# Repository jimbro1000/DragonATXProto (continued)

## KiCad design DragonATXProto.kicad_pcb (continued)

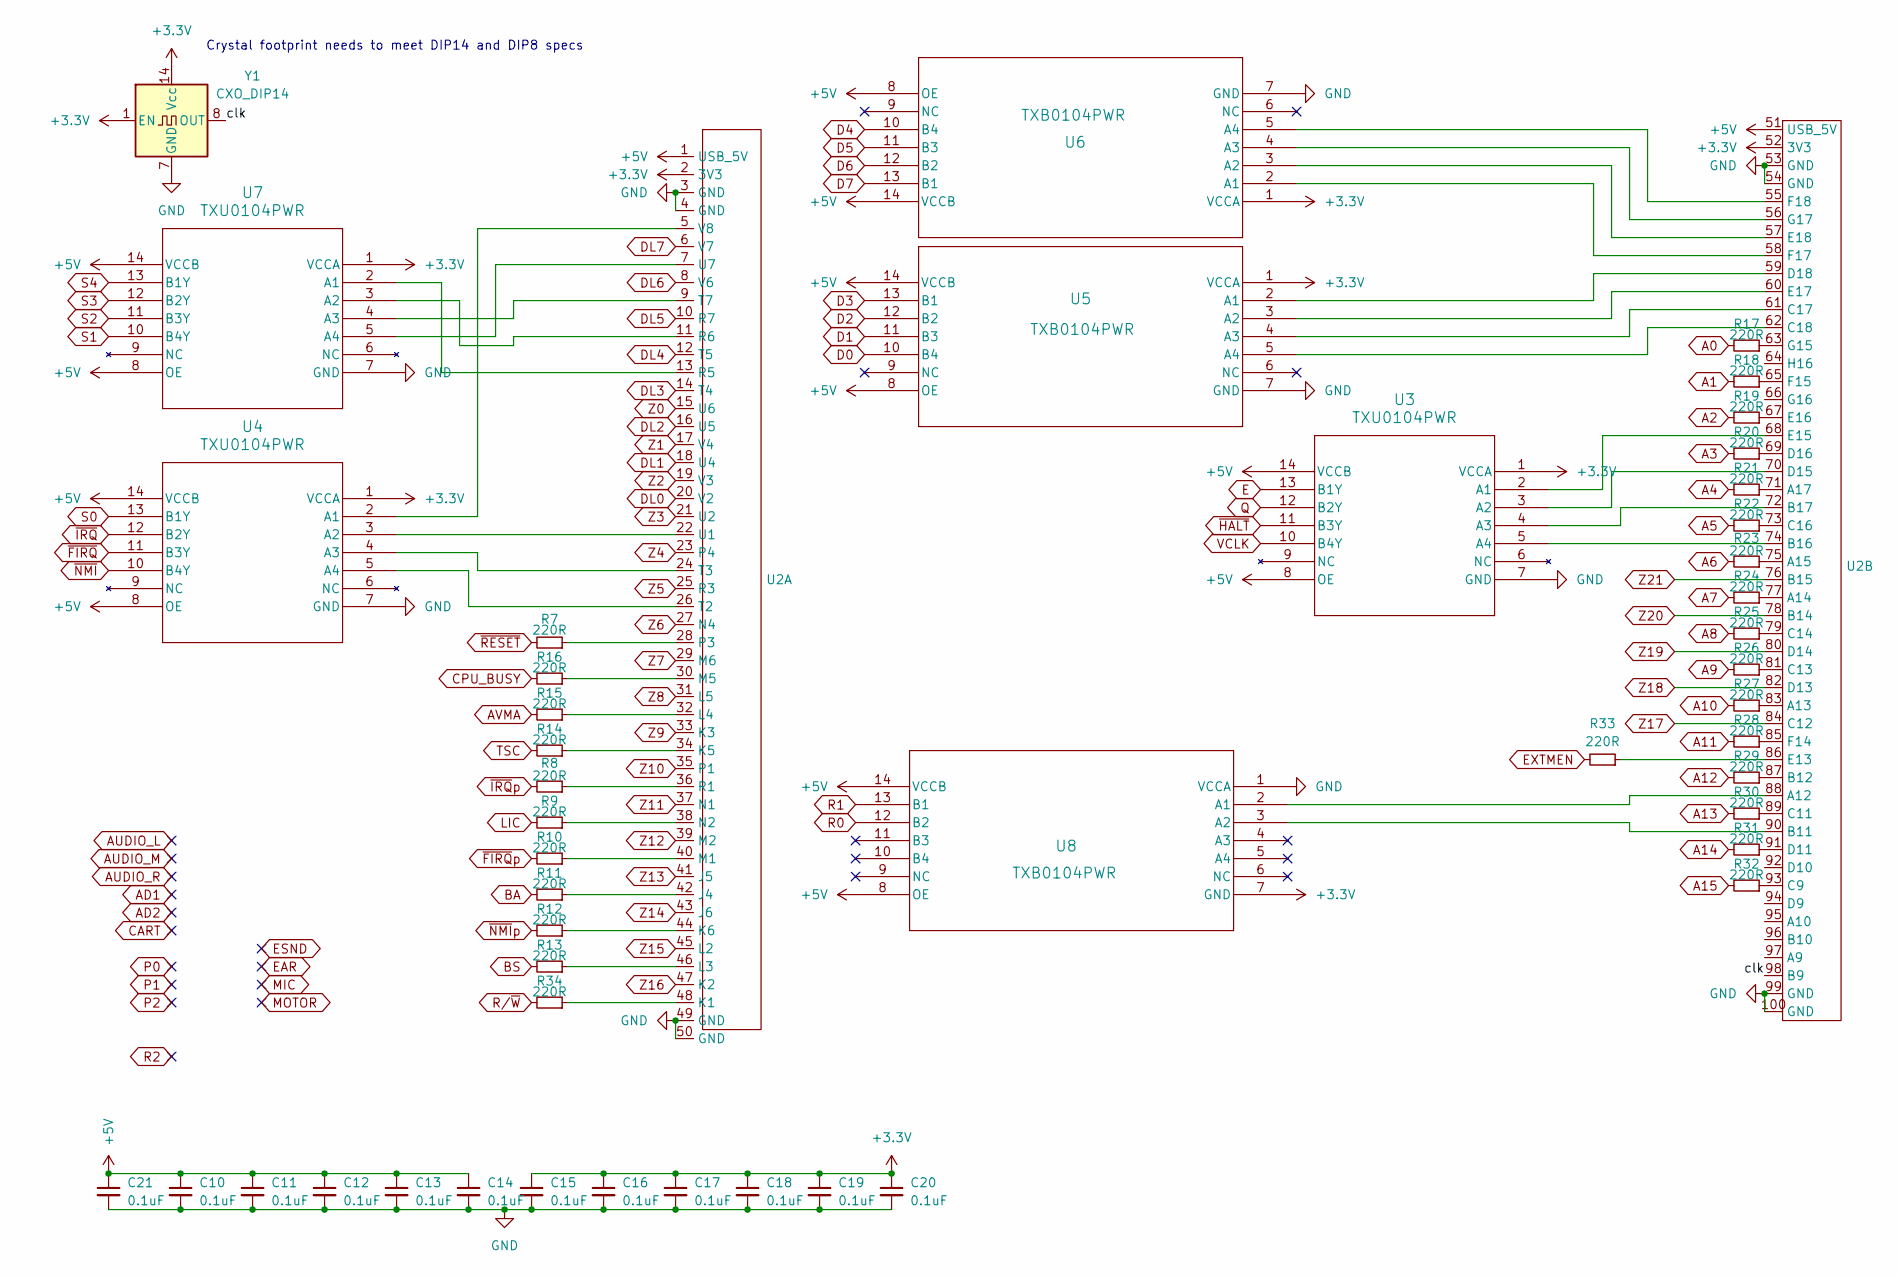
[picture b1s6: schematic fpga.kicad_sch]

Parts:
C10, C11, C12, C13, C14, C15, C16, C17, C18, C19, C20, C21: 0.1uF; C_0603_1608Metric
R7, R8, R9, R10, R11, R12, R13, R14, R15, R16, R17, R18, R19, R20, R21, R22, R23, R24, R25, R26, R27, R28, R29, R30, R31, R32, R33, R34: 220R; R_0603_1608Metric
U2: QMTECH_XC7A15T
U3, U4, U7: TXU0104PWR; TSSOP_0104PWR
U5, U6, U8: TXB0104PWR; TSSOP_0104PWR
Y1: CXO_DIP14; Oscillator_DIP-14

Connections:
+3.3V: C15.1, C16.1, C17.1, C18.1, C19.1, C20.1, U2.2 (3V3), U2.52 (3V3), U3.1 (VCCA), U4.1 (VCCA), U5.1 (VCCA), U6.1 (VCCA), U7.1 (VCCA), U8.7 (GND), Y1.1 (EN), Y1.14 (Vcc); also elsewhere on the board
+5V: C10.1, C11.1, C12.1, C13.1, C14.1, C21.1, U2.1 (USB_5V), U2.51 (USB_5V), U3.8 (OE), U3.14 (VCCB), U4.8 (OE), U4.14 (VCCB), U5.8 (OE), U5.14 (VCCB), U6.8 (OE), U6.14 (VCCB), U7.8 (OE), U7.14 (VCCB), U8.8 (OE), U8.14 (VCCB); also elsewhere on the board
/fpga/clk: U2.98 (B9), Y1.8 (OUT)
A0: R17.2; also elsewhere on the board
A1: R18.2; also elsewhere on the board
A2: R19.2; also elsewhere on the board
A3: R20.2; also elsewhere on the board
A4: R21.2; also elsewhere on the board
A5: R22.2; also elsewhere on the board
A6: R23.2; also elsewhere on the board
A7: R24.2; also elsewhere on the board
A8: R25.2; also elsewhere on the board
A9: R26.2; also elsewhere on the board
A10: R27.2; also elsewhere on the board
A11: R28.2; also elsewhere on the board
A12: R29.2; also elsewhere on the board
A13: R30.2; also elsewhere on the board
A14: R31.2; also elsewhere on the board
A15: R32.2; also elsewhere on the board
AVMA: R15.2; also elsewhere on the board
BA: R11.2; also elsewhere on the board
BS: R13.2; also elsewhere on the board
CPU_BUSY: R16.2; also elsewhere on the board
D0: U5.10 (B4); also elsewhere on the board
D1: U5.11 (B3); also elsewhere on the board
D2: U5.12 (B2); also elsewhere on the board
D3: U5.13 (B1); also elsewhere on the board
D4: U6.10 (B4); also elsewhere on the board
D5: U6.11 (B3); also elsewhere on the board
D6: U6.12 (B2); also elsewhere on the board
D7: U6.13 (B1); also elsewhere on the board
DL0: U2.20 (V2); also elsewhere on the board
DL1: U2.18 (U4); also elsewhere on the board
DL2: U2.16 (U5); also elsewhere on the board
DL3: U2.14 (T4); also elsewhere on the board
DL4: U2.12 (T5); also elsewhere on the board
DL5: U2.10 (R7); also elsewhere on the board
DL6: U2.8 (V6); also elsewhere on the board
DL7: U2.6 (V7); also elsewhere on the board
E: U3.13 (B1Y); also elsewhere on the board
EXTMEN: R33.2; also elsewhere on the board
GND: C10.2, C11.2, C12.2, C13.2, C14.2, C15.2, C16.2, C17.2, C18.2, C19.2, C20.2, C21.2, U2.3 (GND), U2.4 (GND), U2.49 (GND), U2.50 (GND), U2.53 (GND), U2.54 (GND), U2.99 (GND), U2.100 (GND), U3.7 (GND), U4.7 (GND), U5.7 (GND), U6.7 (GND), U7.7 (GND), U8.1 (VCCA), Y1.7 (GND); also elsewhere on the board
LIC: R9.2; also elsewhere on the board
unnamed: R11.1, U2.42 (J4)
unnamed: R34.1, U2.48 (K1)
unnamed: R14.1, U2.34 (K5)
unnamed: R12.1, U2.44 (K6)
unnamed: R13.1, U2.46 (L3)
unnamed: R15.1, U2.32 (L4)
unnamed: R10.1, U2.40 (M1)
unnamed: R16.1, U2.30 (M5)
unnamed: R9.1, U2.38 (N2)
unnamed: R7.1, U2.28 (P3)
unnamed: R8.1, U2.36 (R1)
unnamed: U2.13 (R5), U7.2 (A1)
unnamed: U2.11 (R6), U7.3 (A2)
unnamed: U2.26 (T2), U4.5 (A4)
unnamed: U2.24 (T3), U4.4 (A3)
unnamed: U2.9 (T7), U7.4 (A3)
unnamed: U2.22 (U1), U4.3 (A2)
unnamed: U2.7 (U7), U7.5 (A4)
unnamed: U2.5 (V8), U4.2 (A1)
unnamed: U2.88 (A12), U8.2 (A1)
unnamed: R27.1, U2.83 (A13)
unnamed: R24.1, U2.77 (A14)
unnamed: R23.1, U2.75 (A15)
unnamed: R21.1, U2.71 (A17)
unnamed: U2.90 (B11), U8.3 (A2)
unnamed: R29.1, U2.87 (B12)
unnamed: U2.74 (B16), U3.5 (A4)
unnamed: U2.72 (B17), U3.4 (A3)
unnamed: R32.1, U2.93 (C9)
unnamed: R30.1, U2.89 (C11)
unnamed: R26.1, U2.81 (C13)
unnamed: R25.1, U2.79 (C14)
unnamed: R22.1, U2.73 (C16)
unnamed: U2.61 (C17), U5.4 (A3)
unnamed: U2.62 (C18), U5.5 (A4)
unnamed: R31.1, U2.91 (D11)
unnamed: U2.70 (D15), U3.3 (A2)
unnamed: R20.1, U2.69 (D16)
unnamed: U2.59 (D18), U5.2 (A1)
unnamed: R33.1, U2.86 (E13)
unnamed: U2.68 (E15), U3.2 (A1)
unnamed: R19.1, U2.67 (E16)
unnamed: U2.60 (E17), U5.3 (A2)
unnamed: U2.57 (E18), U6.3 (A2)
unnamed: R28.1, U2.85 (F14)
unnamed: R18.1, U2.65 (F15)
unnamed: U2.58 (F17), U6.2 (A1)
unnamed: U2.55 (F18), U6.5 (A4)
unnamed: R17.1, U2.63 (G15)
unnamed: U2.56 (G17), U6.4 (A3)
Q: U3.12 (B2Y); also elsewhere on the board
R0: U8.12 (B2); also elsewhere on the board
R1: U8.13 (B1); also elsewhere on the board
R/~W: R34.2; also elsewhere on the board
S0: U4.13 (B1Y); also elsewhere on the board
S1: U7.10 (B4Y); also elsewhere on the board
S2: U7.11 (B3Y); also elsewhere on the board
S3: U7.12 (B2Y); also elsewhere on the board
S4: U7.13 (B1Y); also elsewhere on the board
TSC: R14.2; also elsewhere on the board
VCLK: U3.10 (B4Y); also elsewhere on the board
Z0: U2.15 (U6); also elsewhere on the board
Z1: U2.17 (V4); also elsewhere on the board
Z2: U2.19 (V3); also elsewhere on the board
Z3: U2.21 (U2); also elsewhere on the board
Z4: U2.23 (P4); also elsewhere on the board
Z5: U2.25 (R3); also elsewhere on the board
Z6: U2.27 (N4); also elsewhere on the board
Z7: U2.29 (M6); also elsewhere on the board
Z8: U2.31 (L5); also elsewhere on the board
Z9: U2.33 (K3); also elsewhere on the board
Z10: U2.35 (P1); also elsewhere on the board
Z11: U2.37 (N1); also elsewhere on the board
Z12: U2.39 (M2); also elsewhere on the board
Z13: U2.41 (J5); also elsewhere on the board
Z14: U2.43 (J6); also elsewhere on the board
Z15: U2.45 (L2); also elsewhere on the board
Z16: U2.47 (K2); also elsewhere on the board
Z17: U2.84 (C12); also elsewhere on the board
Z18: U2.82 (D13); also elsewhere on the board
Z19: U2.80 (D14); also elsewhere on the board
Z20: U2.78 (B14); also elsewhere on the board
Z21: U2.76 (B15); also elsewhere on the board
~FIRQ: U4.11 (B3Y); also elsewhere on the board
~FIRQp: R10.2; also elsewhere on the board
~HALT: U3.11 (B3Y); also elsewhere on the board
~IRQ: U4.12 (B2Y); also elsewhere on the board
~IRQp: R8.2; also elsewhere on the board
~NMI: U4.10 (B4Y); also elsewhere on the board
~NMIp: R12.2; also elsewhere on the board
~RESET: R7.2; also elsewhere on the board

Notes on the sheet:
Crystal footprint needs to meet DIP14 and DIP8 specs

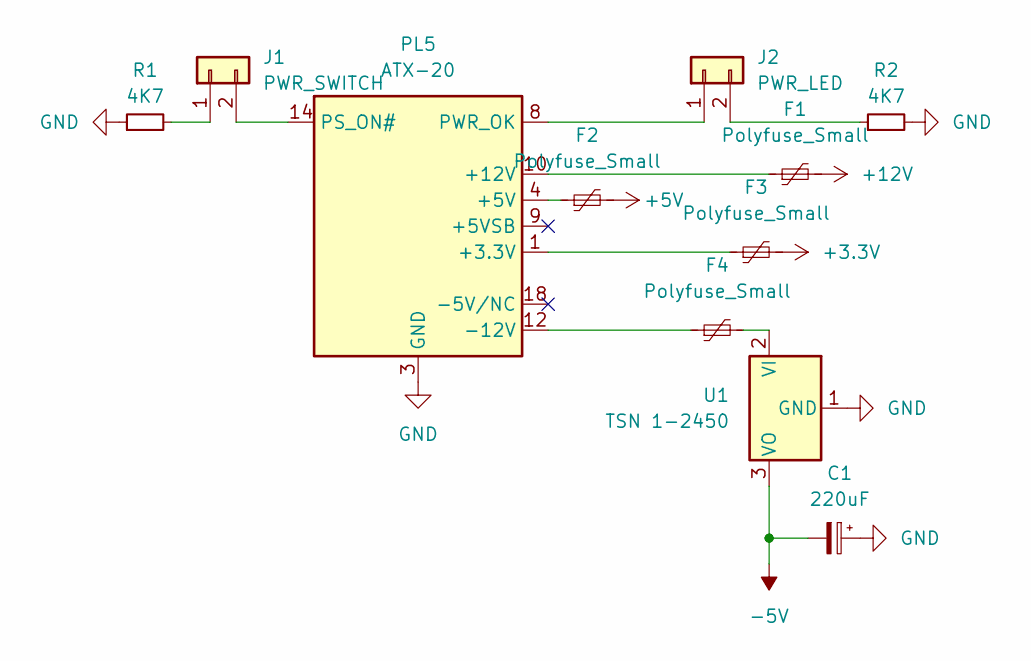
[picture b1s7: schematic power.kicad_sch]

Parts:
C1: 220uF; CP_Radial_D8.0mm_P5.00mm; DigiKey 732-875575345004CT-ND
F1, F2, F3, F4: Polyfuse_Small; Fuse_Bourns_MF-RHT400
J1: PWR_SWITCH; PinHeader_1x02_P2.54mm_Vertical
J2: PWR_LED; PinHeader_1x02_P2.54mm_Vertical
PL5: ATX-20; Molex_Mini-Fit_Jr_5566-20A_2x10_P4.20mm_Vertical
R1, R2: 4K7; R_Axial_DIN0204_L3.6mm_D1.6mm_P2.54mm_Vertical; DigiKey 541-4131-1-ND
U1: TSN 1-2450; TO-220-3_Horizontal_TabDown; DigiKey TSN1-2450-ND

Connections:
+3.3V: F3.2; also elsewhere on the board
+5V: F2.2; also elsewhere on the board
+12V: F1.2; also elsewhere on the board
-5V: C1.2, U1.3 (VO); also elsewhere on the board
GND: C1.1, PL5.3 (GND), PL5.5 (GND), PL5.7 (GND), PL5.13 (GND), PL5.15 (GND), PL5.16 (GND), PL5.17 (GND), R1.1, R2.2, U1.1 (GND); also elsewhere on the board
unnamed: F2.1, PL5.4 (+5V), PL5.6 (+5V), PL5.19 (+5V), PL5.20 (+5V)
unnamed: F3.1, PL5.1 (+3.3V), PL5.2 (+3.3V), PL5.11 (+3.3V)
unnamed: J1.1, R1.2
unnamed: J1.2, PL5.14 (PS_ON#)
unnamed: J2.1, PL5.8 (PWR_OK)
unnamed: J2.2, R2.1
unnamed: F1.1, PL5.10 (+12V)
unnamed: F4.1, PL5.12 (-12V)
unnamed: F4.2, U1.2 (VI)

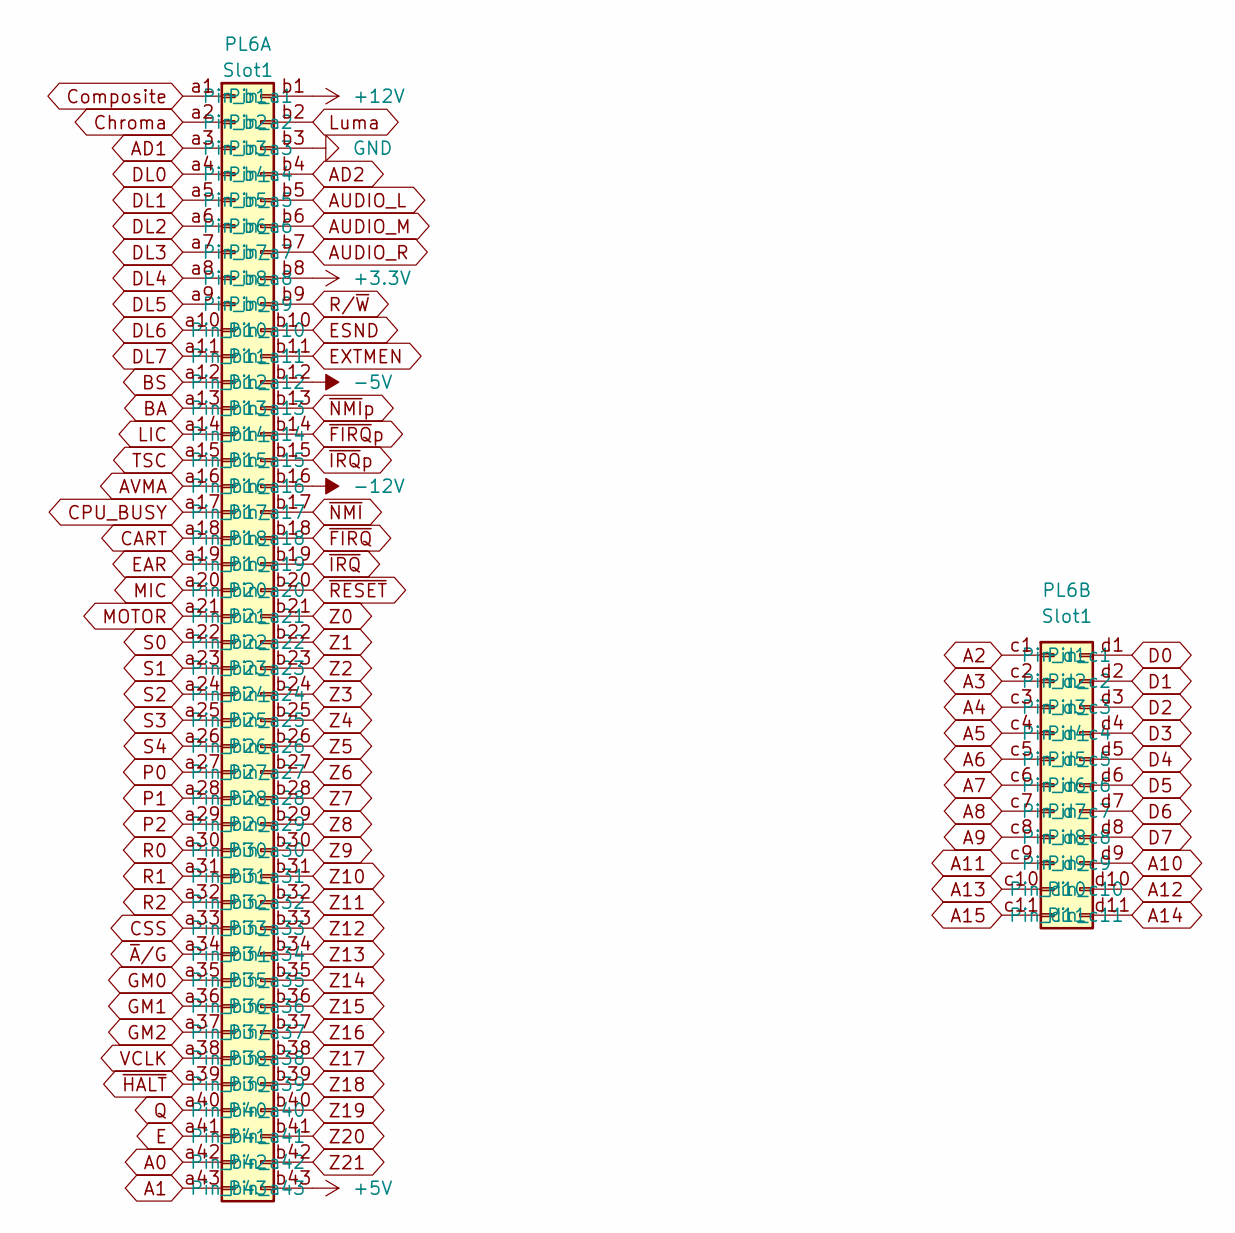
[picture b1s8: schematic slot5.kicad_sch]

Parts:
PL6: Slot1; Card_Edge

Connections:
+3.3V: PL6.b8; also elsewhere on the board
+5V: PL6.b43; also elsewhere on the board
+12V: PL6.b1; also elsewhere on the board
-5V: PL6.b12; also elsewhere on the board
-12V: PL6.b16; also elsewhere on the board
A0: PL6.a42; also elsewhere on the board
A1: PL6.a43; also elsewhere on the board
A2: PL6.c1; also elsewhere on the board
A3: PL6.c2; also elsewhere on the board
A4: PL6.c3; also elsewhere on the board
A5: PL6.c4; also elsewhere on the board
A6: PL6.c5; also elsewhere on the board
A7: PL6.c6; also elsewhere on the board
A8: PL6.c7; also elsewhere on the board
A9: PL6.c8; also elsewhere on the board
A10: PL6.d9; also elsewhere on the board
A11: PL6.c9; also elsewhere on the board
A12: PL6.d10; also elsewhere on the board
A13: PL6.c10; also elsewhere on the board
A14: PL6.d11; also elsewhere on the board
A15: PL6.c11; also elsewhere on the board
AD1: PL6.a3; also elsewhere on the board
AD2: PL6.b4; also elsewhere on the board
AUDIO_L: PL6.b5; also elsewhere on the board
AUDIO_M: PL6.b6; also elsewhere on the board
AUDIO_R: PL6.b7; also elsewhere on the board
AVMA: PL6.a16; also elsewhere on the board
BA: PL6.a13; also elsewhere on the board
BS: PL6.a12; also elsewhere on the board
CART: PL6.a18; also elsewhere on the board
CPU_BUSY: PL6.a17; also elsewhere on the board
CSS: PL6.a33; also elsewhere on the board
Chroma: PL6.a2; also elsewhere on the board
Composite: PL6.a1; also elsewhere on the board
D0: PL6.d1; also elsewhere on the board
D1: PL6.d2; also elsewhere on the board
D2: PL6.d3; also elsewhere on the board
D3: PL6.d4; also elsewhere on the board
D4: PL6.d5; also elsewhere on the board
D5: PL6.d6; also elsewhere on the board
D6: PL6.d7; also elsewhere on the board
D7: PL6.d8; also elsewhere on the board
DL0: PL6.a4; also elsewhere on the board
DL1: PL6.a5; also elsewhere on the board
DL2: PL6.a6; also elsewhere on the board
DL3: PL6.a7; also elsewhere on the board
DL4: PL6.a8; also elsewhere on the board
DL5: PL6.a9; also elsewhere on the board
DL6: PL6.a10; also elsewhere on the board
DL7: PL6.a11; also elsewhere on the board
E: PL6.a41; also elsewhere on the board
EAR: PL6.a19; also elsewhere on the board
ESND: PL6.b10; also elsewhere on the board
EXTMEN: PL6.b11; also elsewhere on the board
GM0: PL6.a35; also elsewhere on the board
GM1: PL6.a36; also elsewhere on the board
GM2: PL6.a37; also elsewhere on the board
GND: PL6.b3; also elsewhere on the board
LIC: PL6.a14; also elsewhere on the board
Luma: PL6.b2; also elsewhere on the board
MIC: PL6.a20; also elsewhere on the board
MOTOR: PL6.a21; also elsewhere on the board
P0: PL6.a27; also elsewhere on the board
P1: PL6.a28; also elsewhere on the board
P2: PL6.a29; also elsewhere on the board
Q: PL6.a40; also elsewhere on the board
R0: PL6.a30; also elsewhere on the board
R1: PL6.a31; also elsewhere on the board
R2: PL6.a32; also elsewhere on the board
R/~W: PL6.b9; also elsewhere on the board
S0: PL6.a22; also elsewhere on the board
S1: PL6.a23; also elsewhere on the board
S2: PL6.a24; also elsewhere on the board
S3: PL6.a25; also elsewhere on the board
S4: PL6.a26; also elsewhere on the board
TSC: PL6.a15; also elsewhere on the board
VCLK: PL6.a38; also elsewhere on the board
Z0: PL6.b21; also elsewhere on the board
Z1: PL6.b22; also elsewhere on the board
Z2: PL6.b23; also elsewhere on the board
Z3: PL6.b24; also elsewhere on the board
Z4: PL6.b25; also elsewhere on the board
Z5: PL6.b26; also elsewhere on the board
Z6: PL6.b27; also elsewhere on the board
Z7: PL6.b28; also elsewhere on the board
Z8: PL6.b29; also elsewhere on the board
Z9: PL6.b30; also elsewhere on the board
Z10: PL6.b31; also elsewhere on the board
Z11: PL6.b32; also elsewhere on the board
Z12: PL6.b33; also elsewhere on the board
Z13: PL6.b34; also elsewhere on the board
Z14: PL6.b35; also elsewhere on the board
Z15: PL6.b36; also elsewhere on the board
Z16: PL6.b37; also elsewhere on the board
Z17: PL6.b38; also elsewhere on the board
Z18: PL6.b39; also elsewhere on the board
Z19: PL6.b40; also elsewhere on the board
Z20: PL6.b41; also elsewhere on the board
Z21: PL6.b42; also elsewhere on the board
~A/G: PL6.a34; also elsewhere on the board
~FIRQ: PL6.b18; also elsewhere on the board
~FIRQp: PL6.b14; also elsewhere on the board
~HALT: PL6.a39; also elsewhere on the board
~IRQ: PL6.b19; also elsewhere on the board
~IRQp: PL6.b15; also elsewhere on the board
~NMI: PL6.b17; also elsewhere on the board
~NMIp: PL6.b13; also elsewhere on the board
~RESET: PL6.b20; also elsewhere on the board

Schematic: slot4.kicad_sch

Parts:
PL4: Slot1; Card_Edge

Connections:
+3.3V: PL4.b8; also elsewhere on the board
+5V: PL4.b43; also elsewhere on the board
+12V: PL4.b1; also elsewhere on the board
-5V: PL4.b12; also elsewhere on the board
-12V: PL4.b16; also elsewhere on the board
A0: PL4.a42; also elsewhere on the board
A1: PL4.a43; also elsewhere on the board
A2: PL4.c1; also elsewhere on the board
A3: PL4.c2; also elsewhere on the board
A4: PL4.c3; also elsewhere on the board
A5: PL4.c4; also elsewhere on the board
A6: PL4.c5; also elsewhere on the board
A7: PL4.c6; also elsewhere on the board
A8: PL4.c7; also elsewhere on the board
A9: PL4.c8; also elsewhere on the board
A10: PL4.d9; also elsewhere on the board
A11: PL4.c9; also elsewhere on the board
A12: PL4.d10; also elsewhere on the board
A13: PL4.c10; also elsewhere on the board
A14: PL4.d11; also elsewhere on the board
A15: PL4.c11; also elsewhere on the board
AD1: PL4.a3; also elsewhere on the board
AD2: PL4.b4; also elsewhere on the board
AUDIO_L: PL4.b5; also elsewhere on the board
AUDIO_M: PL4.b6; also elsewhere on the board
AUDIO_R: PL4.b7; also elsewhere on the board
AVMA: PL4.a16; also elsewhere on the board
BA: PL4.a13; also elsewhere on the board
BS: PL4.a12; also elsewhere on the board
CART: PL4.a18; also elsewhere on the board
CPU_BUSY: PL4.a17; also elsewhere on the board
CSS: PL4.a33; also elsewhere on the board
Chroma: PL4.a2; also elsewhere on the board
Composite: PL4.a1; also elsewhere on the board
D0: PL4.d1; also elsewhere on the board
D1: PL4.d2; also elsewhere on the board
D2: PL4.d3; also elsewhere on the board
D3: PL4.d4; also elsewhere on the board
D4: PL4.d5; also elsewhere on the board
D5: PL4.d6; also elsewhere on the board
D6: PL4.d7; also elsewhere on the board
D7: PL4.d8; also elsewhere on the board
DL0: PL4.a4; also elsewhere on the board
DL1: PL4.a5; also elsewhere on the board
DL2: PL4.a6; also elsewhere on the board
DL3: PL4.a7; also elsewhere on the board
DL4: PL4.a8; also elsewhere on the board
DL5: PL4.a9; also elsewhere on the board
DL6: PL4.a10; also elsewhere on the board
DL7: PL4.a11; also elsewhere on the board
E: PL4.a41; also elsewhere on the board
EAR: PL4.a19; also elsewhere on the board
ESND: PL4.b10; also elsewhere on the board
EXTMEN: PL4.b11; also elsewhere on the board
GM0: PL4.a35; also elsewhere on the board
GM1: PL4.a36; also elsewhere on the board
GM2: PL4.a37; also elsewhere on the board
GND: PL4.b3; also elsewhere on the board
LIC: PL4.a14; also elsewhere on the board
Luma: PL4.b2; also elsewhere on the board
MIC: PL4.a20; also elsewhere on the board
MOTOR: PL4.a21; also elsewhere on the board
P0: PL4.a27; also elsewhere on the board
P1: PL4.a28; also elsewhere on the board
P2: PL4.a29; also elsewhere on the board
Q: PL4.a40; also elsewhere on the board
R0: PL4.a30; also elsewhere on the board
R1: PL4.a31; also elsewhere on the board
R2: PL4.a32; also elsewhere on the board
R/~W: PL4.b9; also elsewhere on the board
S0: PL4.a22; also elsewhere on the board
S1: PL4.a23; also elsewhere on the board
S2: PL4.a24; also elsewhere on the board
S3: PL4.a25; also elsewhere on the board
S4: PL4.a26; also elsewhere on the board
TSC: PL4.a15; also elsewhere on the board
VCLK: PL4.a38; also elsewhere on the board
Z0: PL4.b21; also elsewhere on the board
Z1: PL4.b22; also elsewhere on the board
Z2: PL4.b23; also elsewhere on the board
Z3: PL4.b24; also elsewhere on the board
Z4: PL4.b25; also elsewhere on the board
Z5: PL4.b26; also elsewhere on the board
Z6: PL4.b27; also elsewhere on the board
Z7: PL4.b28; also elsewhere on the board
Z8: PL4.b29; also elsewhere on the board
Z9: PL4.b30; also elsewhere on the board
Z10: PL4.b31; also elsewhere on the board
Z11: PL4.b32; also elsewhere on the board
Z12: PL4.b33; also elsewhere on the board
Z13: PL4.b34; also elsewhere on the board
Z14: PL4.b35; also elsewhere on the board
Z15: PL4.b36; also elsewhere on the board
Z16: PL4.b37; also elsewhere on the board
Z17: PL4.b38; also elsewhere on the board
Z18: PL4.b39; also elsewhere on the board
Z19: PL4.b40; also elsewhere on the board
Z20: PL4.b41; also elsewhere on the board
Z21: PL4.b42; also elsewhere on the board
~A/G: PL4.a34; also elsewhere on the board
~FIRQ: PL4.b18; also elsewhere on the board
~FIRQp: PL4.b14; also elsewhere on the board
~HALT: PL4.a39; also elsewhere on the board
~IRQ: PL4.b19; also elsewhere on the board
~IRQp: PL4.b15; also elsewhere on the board
~NMI: PL4.b17; also elsewhere on the board
~NMIp: PL4.b13; also elsewhere on the board
~RESET: PL4.b20; also elsewhere on the board

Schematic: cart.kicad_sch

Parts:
J4: CARTRIDGE EDGE; PinHeader_2x20_P2.54mm_Vertical; DigiKey S3315-ND

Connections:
+5V: J4.9; also elsewhere on the board
+12V: J4.1, J4.2; also elsewhere on the board
A0: J4.19; also elsewhere on the board
A1: J4.20; also elsewhere on the board
A2: J4.21; also elsewhere on the board
A3: J4.22; also elsewhere on the board
A4: J4.23; also elsewhere on the board
A5: J4.24; also elsewhere on the board
A6: J4.25; also elsewhere on the board
A7: J4.26; also elsewhere on the board
A8: J4.27; also elsewhere on the board
A9: J4.28; also elsewhere on the board
A10: J4.29; also elsewhere on the board
A11: J4.30; also elsewhere on the board
A12: J4.31; also elsewhere on the board
A13: J4.37; also elsewhere on the board
A14: J4.38; also elsewhere on the board
A15: J4.39; also elsewhere on the board
CART: J4.8; also elsewhere on the board
D0: J4.10; also elsewhere on the board
D1: J4.11; also elsewhere on the board
D2: J4.12; also elsewhere on the board
D3: J4.13; also elsewhere on the board
D4: J4.14; also elsewhere on the board
D5: J4.15; also elsewhere on the board
D6: J4.16; also elsewhere on the board
D7: J4.17; also elsewhere on the board
E: J4.7; also elsewhere on the board
ESND: J4.35; also elsewhere on the board
EXTMEN: J4.40; also elsewhere on the board
GND: J4.33, J4.34; also elsewhere on the board
P2: J4.36; also elsewhere on the board
Q: J4.6; also elsewhere on the board
R2: J4.32; also elsewhere on the board
R/~W: J4.18; also elsewhere on the board
~HALT: J4.3; also elsewhere on the board
~NMIp: J4.4; also elsewhere on the board
~RESET: J4.5; also elsewhere on the board

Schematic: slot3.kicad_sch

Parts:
PL3: Slot1; Card_Edge

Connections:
+3.3V: PL3.b8; also elsewhere on the board
+5V: PL3.b43; also elsewhere on the board
+12V: PL3.b1; also elsewhere on the board
-5V: PL3.b12; also elsewhere on the board
-12V: PL3.b16; also elsewhere on the board
A0: PL3.a42; also elsewhere on the board
A1: PL3.a43; also elsewhere on the board
A2: PL3.c1; also elsewhere on the board
A3: PL3.c2; also elsewhere on the board
A4: PL3.c3; also elsewhere on the board
A5: PL3.c4; also elsewhere on the board
A6: PL3.c5; also elsewhere on the board
A7: PL3.c6; also elsewhere on the board
A8: PL3.c7; also elsewhere on the board
A9: PL3.c8; also elsewhere on the board
A10: PL3.d9; also elsewhere on the board
A11: PL3.c9; also elsewhere on the board
A12: PL3.d10; also elsewhere on the board
A13: PL3.c10; also elsewhere on the board
A14: PL3.d11; also elsewhere on the board
A15: PL3.c11; also elsewhere on the board
AD1: PL3.a3; also elsewhere on the board
AD2: PL3.b4; also elsewhere on the board
AUDIO_L: PL3.b5; also elsewhere on the board
AUDIO_M: PL3.b6; also elsewhere on the board
AUDIO_R: PL3.b7; also elsewhere on the board
AVMA: PL3.a16; also elsewhere on the board
BA: PL3.a13; also elsewhere on the board
BS: PL3.a12; also elsewhere on the board
CART: PL3.a18; also elsewhere on the board
CPU_BUSY: PL3.a17; also elsewhere on the board
CSS: PL3.a33; also elsewhere on the board
Chroma: PL3.a2; also elsewhere on the board
Composite: PL3.a1; also elsewhere on the board
D0: PL3.d1; also elsewhere on the board
D1: PL3.d2; also elsewhere on the board
D2: PL3.d3; also elsewhere on the board
D3: PL3.d4; also elsewhere on the board
D4: PL3.d5; also elsewhere on the board
D5: PL3.d6; also elsewhere on the board
D6: PL3.d7; also elsewhere on the board
D7: PL3.d8; also elsewhere on the board
DL0: PL3.a4; also elsewhere on the board
DL1: PL3.a5; also elsewhere on the board
DL2: PL3.a6; also elsewhere on the board
DL3: PL3.a7; also elsewhere on the board
DL4: PL3.a8; also elsewhere on the board
DL5: PL3.a9; also elsewhere on the board
DL6: PL3.a10; also elsewhere on the board
DL7: PL3.a11; also elsewhere on the board
E: PL3.a41; also elsewhere on the board
EAR: PL3.a19; also elsewhere on the board
ESND: PL3.b10; also elsewhere on the board
EXTMEN: PL3.b11; also elsewhere on the board
GM0: PL3.a35; also elsewhere on the board
GM1: PL3.a36; also elsewhere on the board
GM2: PL3.a37; also elsewhere on the board
GND: PL3.b3; also elsewhere on the board
LIC: PL3.a14; also elsewhere on the board
Luma: PL3.b2; also elsewhere on the board
MIC: PL3.a20; also elsewhere on the board
MOTOR: PL3.a21; also elsewhere on the board
P0: PL3.a27; also elsewhere on the board
P1: PL3.a28; also elsewhere on the board
P2: PL3.a29; also elsewhere on the board
Q: PL3.a40; also elsewhere on the board
R0: PL3.a30; also elsewhere on the board
R1: PL3.a31; also elsewhere on the board
R2: PL3.a32; also elsewhere on the board
R/~W: PL3.b9; also elsewhere on the board
S0: PL3.a22; also elsewhere on the board
S1: PL3.a23; also elsewhere on the board
S2: PL3.a24; also elsewhere on the board
S3: PL3.a25; also elsewhere on the board
S4: PL3.a26; also elsewhere on the board
TSC: PL3.a15; also elsewhere on the board
VCLK: PL3.a38; also elsewhere on the board
Z0: PL3.b21; also elsewhere on the board
Z1: PL3.b22; also elsewhere on the board
Z2: PL3.b23; also elsewhere on the board
Z3: PL3.b24; also elsewhere on the board
Z4: PL3.b25; also elsewhere on the board
Z5: PL3.b26; also elsewhere on the board
Z6: PL3.b27; also elsewhere on the board
Z7: PL3.b28; also elsewhere on the board
Z8: PL3.b29; also elsewhere on the board
Z9: PL3.b30; also elsewhere on the board
Z10: PL3.b31; also elsewhere on the board
Z11: PL3.b32; also elsewhere on the board
Z12: PL3.b33; also elsewhere on the board
Z13: PL3.b34; also elsewhere on the board
Z14: PL3.b35; also elsewhere on the board
Z15: PL3.b36; also elsewhere on the board
Z16: PL3.b37; also elsewhere on the board
Z17: PL3.b38; also elsewhere on the board
Z18: PL3.b39; also elsewhere on the board
Z19: PL3.b40; also elsewhere on the board
Z20: PL3.b41; also elsewhere on the board
Z21: PL3.b42; also elsewhere on the board
~A/G: PL3.a34; also elsewhere on the board
~FIRQ: PL3.b18; also elsewhere on the board
~FIRQp: PL3.b14; also elsewhere on the board
~HALT: PL3.a39; also elsewhere on the board
~IRQ: PL3.b19; also elsewhere on the board
~IRQp: PL3.b15; also elsewhere on the board
~NMI: PL3.b17; also elsewhere on the board
~NMIp: PL3.b13; also elsewhere on the board
~RESET: PL3.b20; also elsewhere on the board

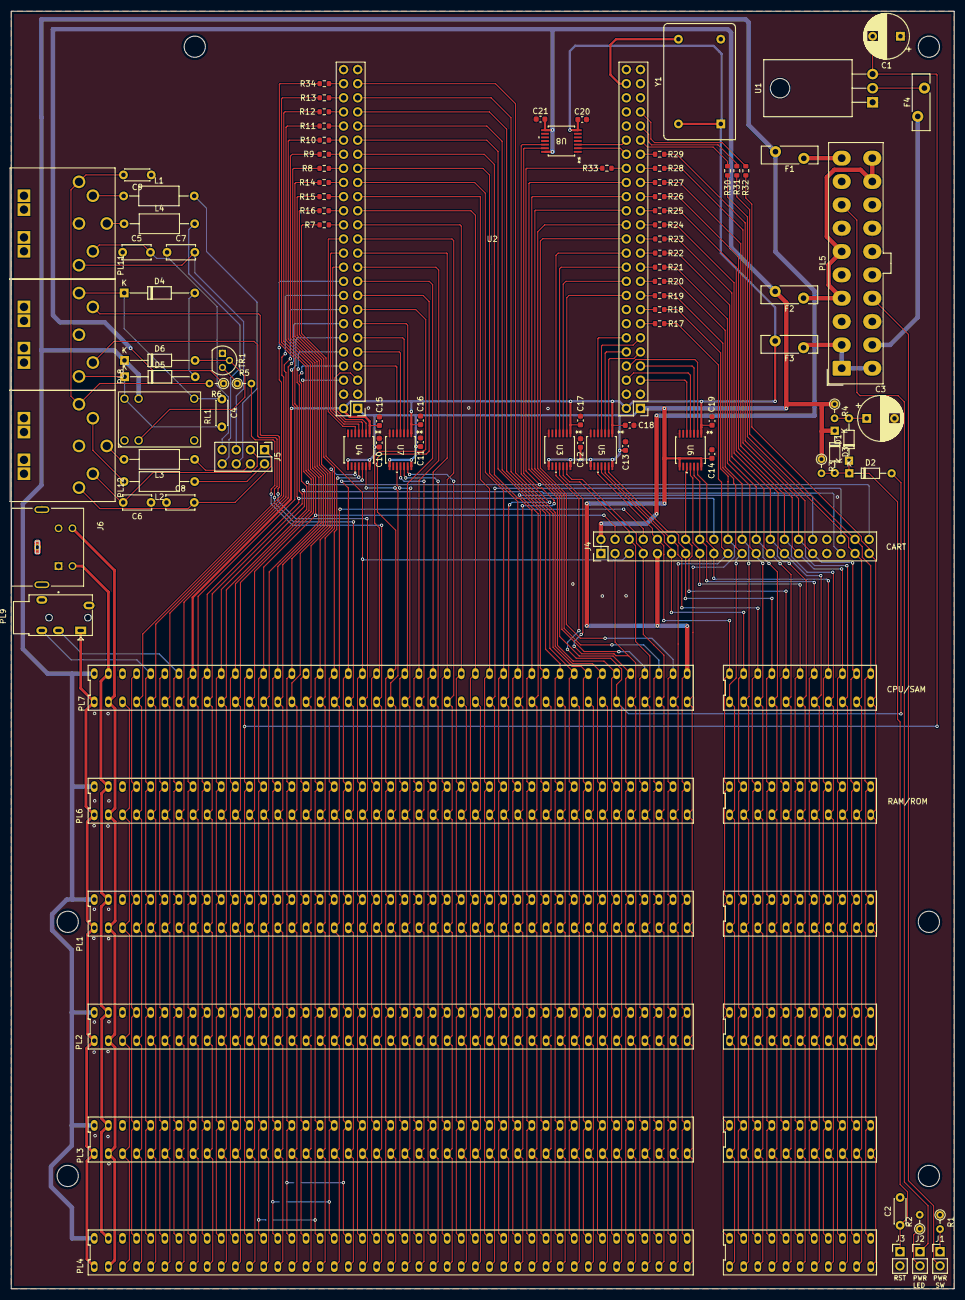
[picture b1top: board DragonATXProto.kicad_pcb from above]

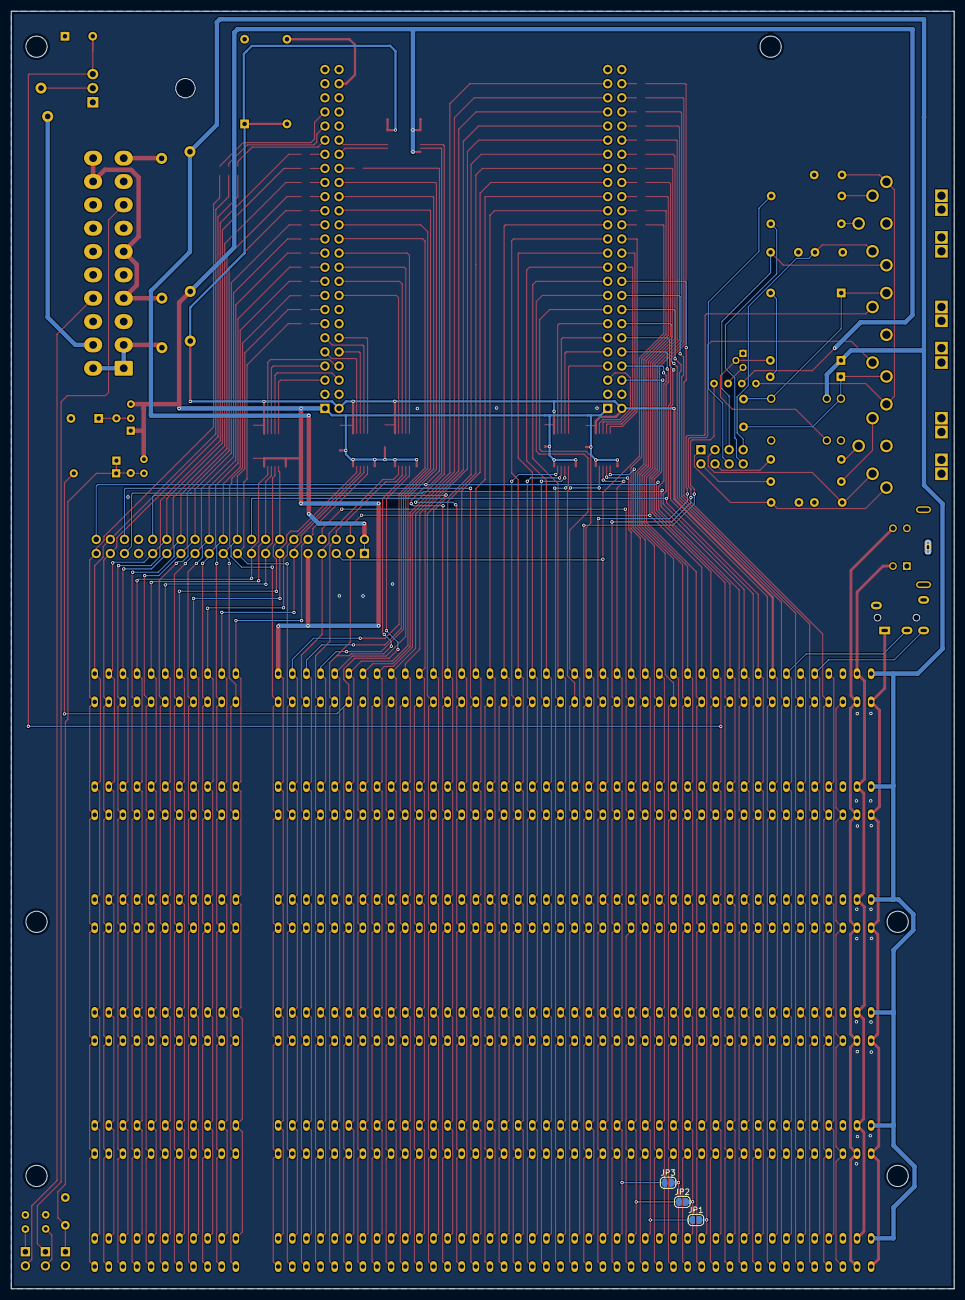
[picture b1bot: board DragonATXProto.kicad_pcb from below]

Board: 2 copper layers, 169.6 x 229.8 mm, 100 parts (3 on the bottom side), 188 nets.

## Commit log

2025-02-17 board layout
2025-02-20 add notes
2025-03-21 revise bus tracing
2025-03-21 reinforce level shifting
